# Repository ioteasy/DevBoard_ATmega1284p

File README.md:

# DevBoard_ATmega1284p
Development board with ATmega1284p (ATmega644pa)

## Features ATmega1284p (ATmega644pa)
- Program Memory 128KB (64KB)
- SRAM 16KB (4KB)
- EEPROM 4KB (2KB)
- 2x UART, 3x SPI, 1x I2C
- 2.5V references
- 2x LED
- ISP
- Arduino  Bootloader via Bluetooth

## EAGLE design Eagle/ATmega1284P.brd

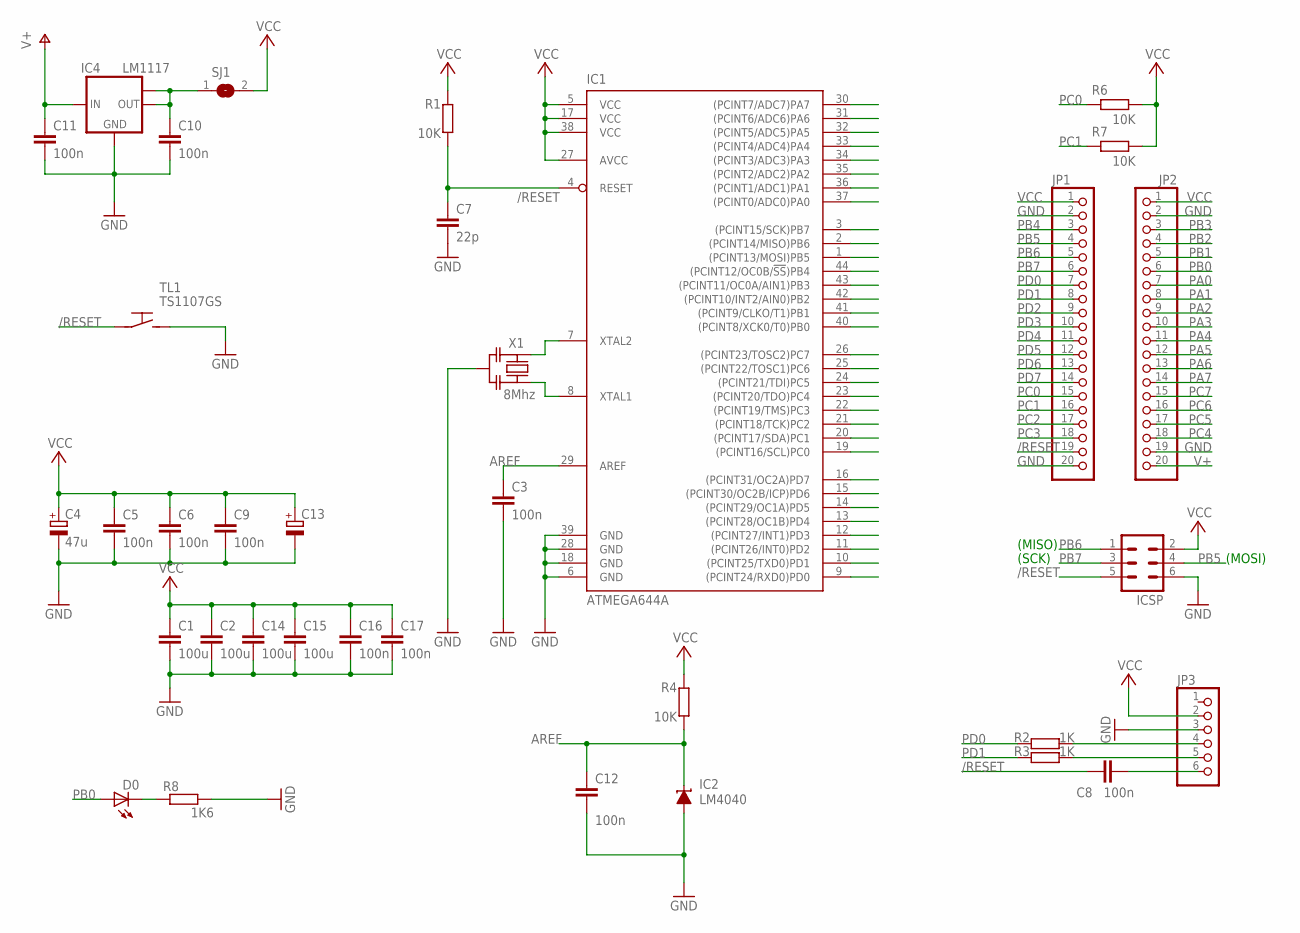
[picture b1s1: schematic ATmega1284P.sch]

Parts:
C1, C2, C14, C15: 100u; C1206
C3, C5, C6, C8, C9, C10, C11, C12, C16, C17: 100n; C0805
C4: 47u; SMC_A
C7: 22p; C0805
C13: CPOL-EUSMCC; SMC_C
D0: LEDCHIPLED_0805; CHIPLED_0805
IC1: ATMEGA644A; TQFP44
IC2: LM4040; DBZ_R-PDSO-G3
IC4: LM1117; SOT223
ICSP: ML6
JP1, JP2: PINHD-1X20; 1X20
JP3: PINHD-1X6; 1X06
R1, R4, R6, R7: 10K; M0805
R2, R3: 1K; M0805
R8: 1K6; M0805
SJ1: SJ
TL1: TS1107GS
X1: 8Mhz; CERALOCK_CSTCE_G

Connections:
/RESET: C7.2, C8.2, IC1.4 (RESET), ICSP.5, JP1.19, R1.1, TL1.P$1
AREF: C3.2, C12.1, IC1.29 (AREF), IC2.1 (C), R4.1
GND: C1.2, C2.2, C3.1, C4.-, C5.1, C6.1, C7.1, C9.1, C10.2, C11.2, C12.2, C13.-, C14.2, C15.2, C16.1, C17.1, IC1.6 (GND), IC1.18 (GND), IC1.28 (GND), IC1.39 (GND), IC2.2 (A), IC4.1 (GND), ICSP.6, JP1.2, JP1.20, JP2.2, JP2.19, JP3.3, R8.1, TL1.P$2 (S), X1.P$2 (GND)
unnamed: C8.1, JP3.6
unnamed: D0.C, R8.2
unnamed: IC1.7 (XTAL2), X1.P$3 (2)
unnamed: IC1.8 (XTAL1), X1.P$1 (1)
unnamed: C10.1, IC4.2 (OUT), IC4.TAB (OUT1), SJ1.1
PA0: IC1.37 ((PCINT0/ADC0)PA0), JP2.7
PA1: IC1.36 ((PCINT1/ADC1)PA1), JP2.8
PA2: IC1.35 ((PCINT2/ADC2)PA2), JP2.9
PA3: IC1.34 ((PCINT3/ADC3)PA3), JP2.10
PA4: IC1.33 ((PCINT4/ADC4)PA4), JP2.11
PA5: IC1.32 ((PCINT5/ADC5)PA5), JP2.12
PA6: IC1.31 ((PCINT6/ADC6)PA6), JP2.13
PA7: IC1.30 ((PCINT7/ADC7)PA7), JP2.14
PB0: D0.A, IC1.40 ((PCINT8/XCK0/T0)PB0), JP2.6
PB1: IC1.41 ((PCINT9/CLKO/T1)PB1), JP2.5
PB2: IC1.42 ((PCINT10/INT2/AIN0)PB2), JP2.4
PB3: IC1.43 ((PCINT11/OC0A/AIN1)PB3), JP2.3
PB4: IC1.44 ((PCINT12/OC0B/!SS!)PB4), JP1.3
PB5: IC1.1 ((PCINT13/MOSI)PB5), ICSP.4, JP1.4
PB6: IC1.2 ((PCINT14/MISO)PB6), ICSP.1, JP1.5
PB7: IC1.3 ((PCINT15/SCK)PB7), ICSP.3, JP1.6
PC0: IC1.19 ((PCINT16/SCL)PC0), JP1.15, R6.1
PC1: IC1.20 ((PCINT17/SDA)PC1), JP1.16, R7.1
PC2: IC1.21 ((PCINT18/TCK)PC2), JP1.17
PC3: IC1.22 ((PCINT19/TMS)PC3), JP1.18
PC4: IC1.23 ((PCINT20/TDO)PC4), JP2.18
PC5: IC1.24 ((PCINT21/TDI)PC5), JP2.17
PC6: IC1.25 ((PCINT22/TOSC1)PC6), JP2.16
PC7: IC1.26 ((PCINT23/TOSC2)PC7), JP2.15
PD0: IC1.9 ((PCINT24/RXD0)PD0), JP1.7, R2.2
PD1: IC1.10 ((PCINT25/TXD0)PD1), JP1.8, R3.2
PD2: IC1.11 ((PCINT26/INT0)PD2), JP1.9
PD3: IC1.12 ((PCINT27/INT1)PD3), JP1.10
PD4: IC1.13 ((PCINT28/OC1B)PD4), JP1.11
PD5: IC1.14 ((PCINT29/OC1A)PD5), JP1.12
PD6: IC1.15 ((PCINT30/OC2B/ICP)PD6), JP1.13
PD7: IC1.16 ((PCINT31/OC2A)PD7), JP1.14
RXD0: JP3.4, R2.1
TXD0: JP3.5, R3.1
V+: C11.1, IC4.3 (IN), JP2.20
VCC: C1.1, C2.1, C4.+, C5.2, C6.2, C9.2, C13.+, C14.1, C15.1, C16.2, C17.2, IC1.5 (VCC), IC1.17 (VCC), IC1.27 (AVCC), IC1.38 (VCC), ICSP.2, JP1.1, JP2.1, JP3.2, R1.2, R4.2, R6.2, R7.2, SJ1.2

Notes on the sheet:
(MOSI)
(MISO)
(SCK)

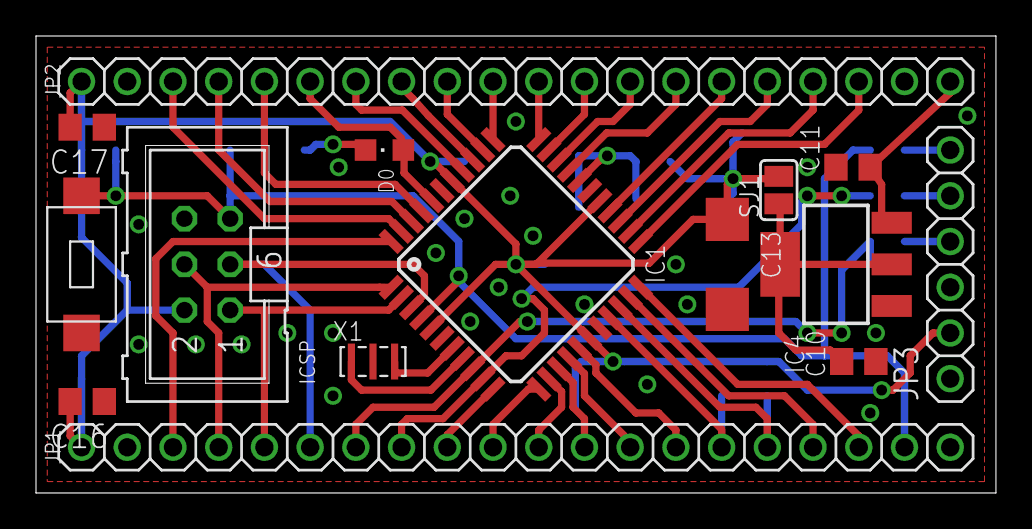
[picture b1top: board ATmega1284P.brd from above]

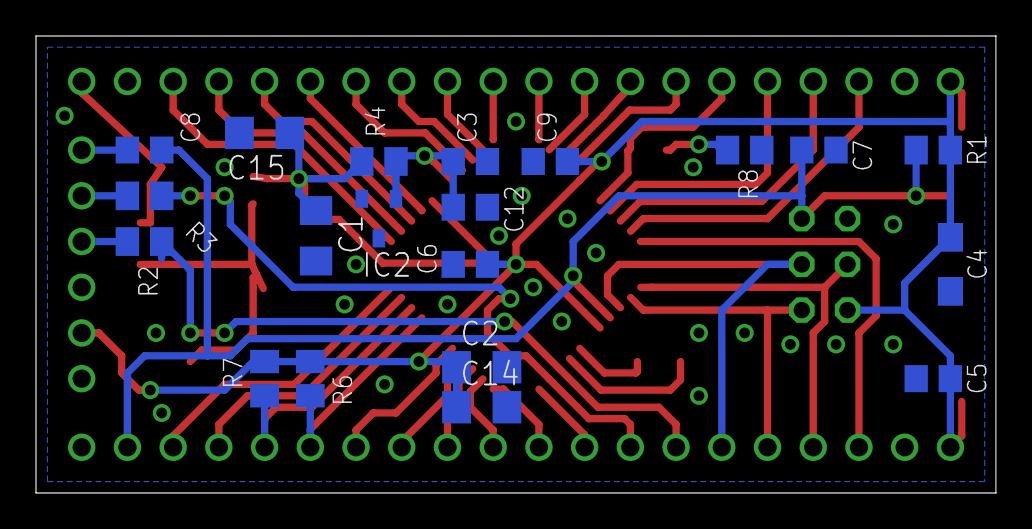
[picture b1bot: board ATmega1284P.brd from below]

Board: 2 copper layers, 53.3 x 25.4 mm, 35 parts (20 on the bottom side), 44 nets.

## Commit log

2018-06-22 Changed voltage reference to LM4040 Changed THT crystal to SMT resonator Added a few capacitors
